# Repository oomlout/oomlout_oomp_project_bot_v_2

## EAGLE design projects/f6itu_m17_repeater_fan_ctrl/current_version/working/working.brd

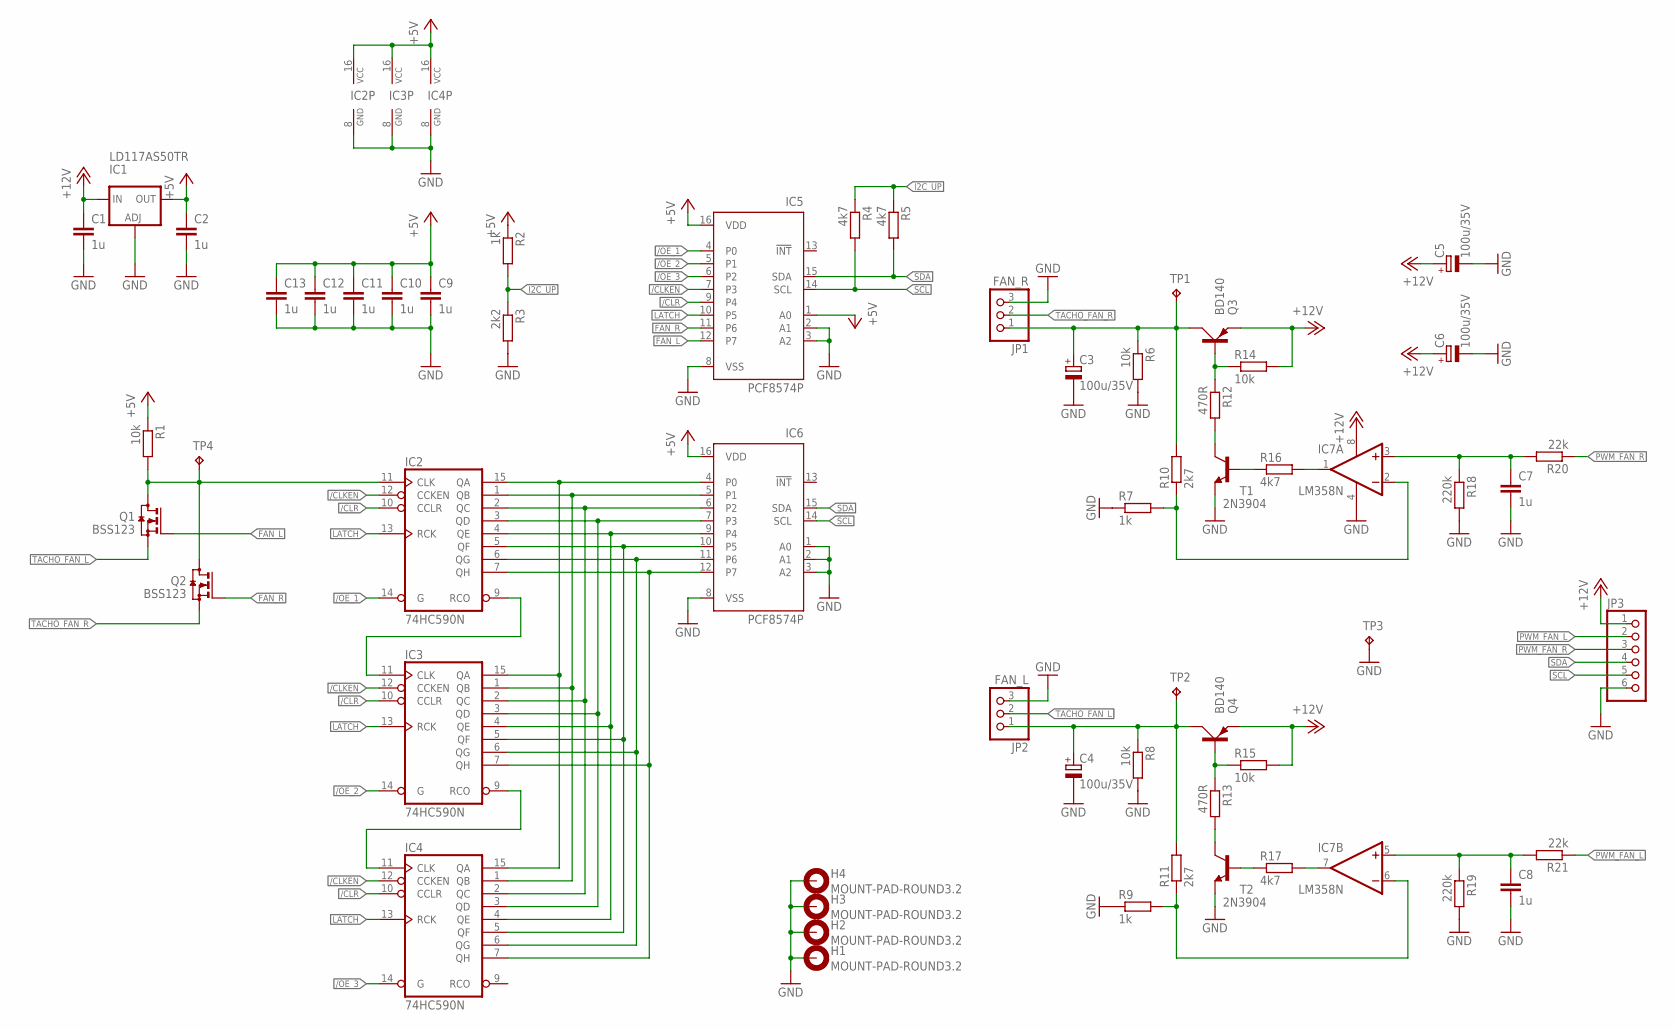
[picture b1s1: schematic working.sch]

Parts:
C1, C2, C7, C8, C9, C10, C11, C12, C13: 1u; C0805
C3, C4, C5, C6: 100u/35V; E3,5-8
H1, H2, H3, H4: MOUNT-PAD-ROUND3.2; 3,2-PAD
IC1: LD117AS50TR; SOT223
IC2, IC3, IC4: 74HC590N; DIL16
IC5, IC6: PCF8574P; DIL16
IC7: LM358N; DIL08
JP1: FAN_R; 1X03
JP2: FAN_L; 1X03
JP3: PINHD-1X6; 1X06
Q1, Q2: BSS123; SOT23
Q3, Q4: BD140; TO126AV
R1, R6, R8, R14, R15: 10k; R0805
R2, R7, R9: 1k; R0805
R3: 2k2; R0805
R4, R5, R16, R17: 4k7; R0805
R10, R11: 2k7; R0805
R12, R13: 470R; R0805
R18, R19: 220k; R0805
R20, R21: 22k; R0805
T1, T2: 2N3904; TO92-EBC
TP1, TP2, TP3, TP4: TPB2,54; B2,54

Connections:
+5V: C2.1, C9.1, C10.1, C11.1, C12.1, C13.1, IC1.4 (OUT), IC2.16 (VCC), IC3.16 (VCC), IC4.16 (VCC), IC5.1 (A0), IC5.16 (VDD), IC6.16 (VDD), R1.1, R2.1
+12V: C1.1, C5.+, C6.+, IC1.3 (IN), IC7.8 (V+), JP3.1, Q3.E, Q4.E, R14.2, R15.2
/CLKEN: IC2.12 (CCKEN), IC3.12 (CCKEN), IC4.12 (CCKEN), IC5.7 (P3)
/CLR: IC2.10 (CCLR), IC3.10 (CCLR), IC4.10 (CCLR), IC5.9 (P4)
/OE_1: IC2.14 (G), IC5.4 (P0)
/OE_2: IC3.14 (G), IC5.5 (P1)
/OE_3: IC4.14 (G), IC5.6 (P2)
FAN_L: IC5.12 (P7), Q1.1 (G)
FAN_R: IC5.11 (P6), Q2.1 (G)
GND: C1.2, C2.2, C3.-, C4.-, C5.-, C6.-, C7.2, C8.2, C9.2, C10.2, C11.2, C12.2, C13.2, H1.B3,2, H2.B3,2, H3.B3,2, H4.B3,2, IC1.1 (ADJ), IC2.8 (GND), IC3.8 (GND), IC4.8 (GND), IC5.2 (A1), IC5.3 (A2), IC5.8 (VSS), IC6.1 (A0), IC6.2 (A1), IC6.3 (A2), IC6.8 (VSS), IC7.4 (V-), JP1.3, JP2.3, JP3.6, R3.2, R6.2, R7.1, R8.2, R9.1, R18.2, R19.2, T1.E, T2.E, TP3.TP
I2C_UP: R2.2, R3.1, R4.1, R5.1
LATCH: IC2.13 (RCK), IC3.13 (RCK), IC4.13 (RCK), IC5.10 (P5)
unnamed: IC2.15 (QA), IC3.15 (QA), IC4.15 (QA), IC6.4 (P0)
unnamed: IC2.1 (QB), IC3.1 (QB), IC4.1 (QB), IC6.5 (P1)
unnamed: IC2.2 (QC), IC3.2 (QC), IC4.2 (QC), IC6.6 (P2)
unnamed: IC2.3 (QD), IC3.3 (QD), IC4.3 (QD), IC6.7 (P3)
unnamed: IC2.4 (QE), IC3.4 (QE), IC4.4 (QE), IC6.9 (P4)
unnamed: IC2.11 (CLK), Q1.3 (D), Q2.3 (D), R1.2, TP4.TP
unnamed: IC2.6 (QG), IC3.6 (QG), IC4.6 (QG), IC6.11 (P6)
unnamed: C7.1, IC7.3 (+IN), R18.1, R20.2
unnamed: R12.2, T1.C
unnamed: C8.1, IC7.5 (+IN), R19.1, R21.2
unnamed: Q3.B, R12.1, R14.1
unnamed: IC3.9 (RCO), IC4.11 (CLK)
unnamed: R13.2, T2.C
unnamed: C3.+, JP1.1, Q3.C, R6.1, R10.2, TP1.TP
unnamed: IC7.6 (-IN), R9.2, R11.1
unnamed: Q4.B, R13.1, R15.1
unnamed: R16.1, T1.B
unnamed: C4.+, JP2.1, Q4.C, R8.1, R11.2, TP2.TP
unnamed: IC7.2 (-IN), R7.2, R10.1
unnamed: IC7.1 (OUT), R16.2
unnamed: R17.1, T2.B
unnamed: IC7.7 (OUT), R17.2
unnamed: IC2.9 (RCO), IC3.11 (CLK)
unnamed: IC2.5 (QF), IC3.5 (QF), IC4.5 (QF), IC6.10 (P5)
unnamed: IC2.7 (QH), IC3.7 (QH), IC4.7 (QH), IC6.12 (P7)
PWM_FAN_L: JP3.2, R21.1
PWM_FAN_R: JP3.3, R20.1
SCL: IC5.14 (SCL), IC6.14 (SCL), JP3.5, R4.2
SDA: IC5.15 (SDA), IC6.15 (SDA), JP3.4, R5.2
TACHO_FAN_L: JP2.2, Q1.2 (S)
TACHO_FAN_R: JP1.2, Q2.2 (S)

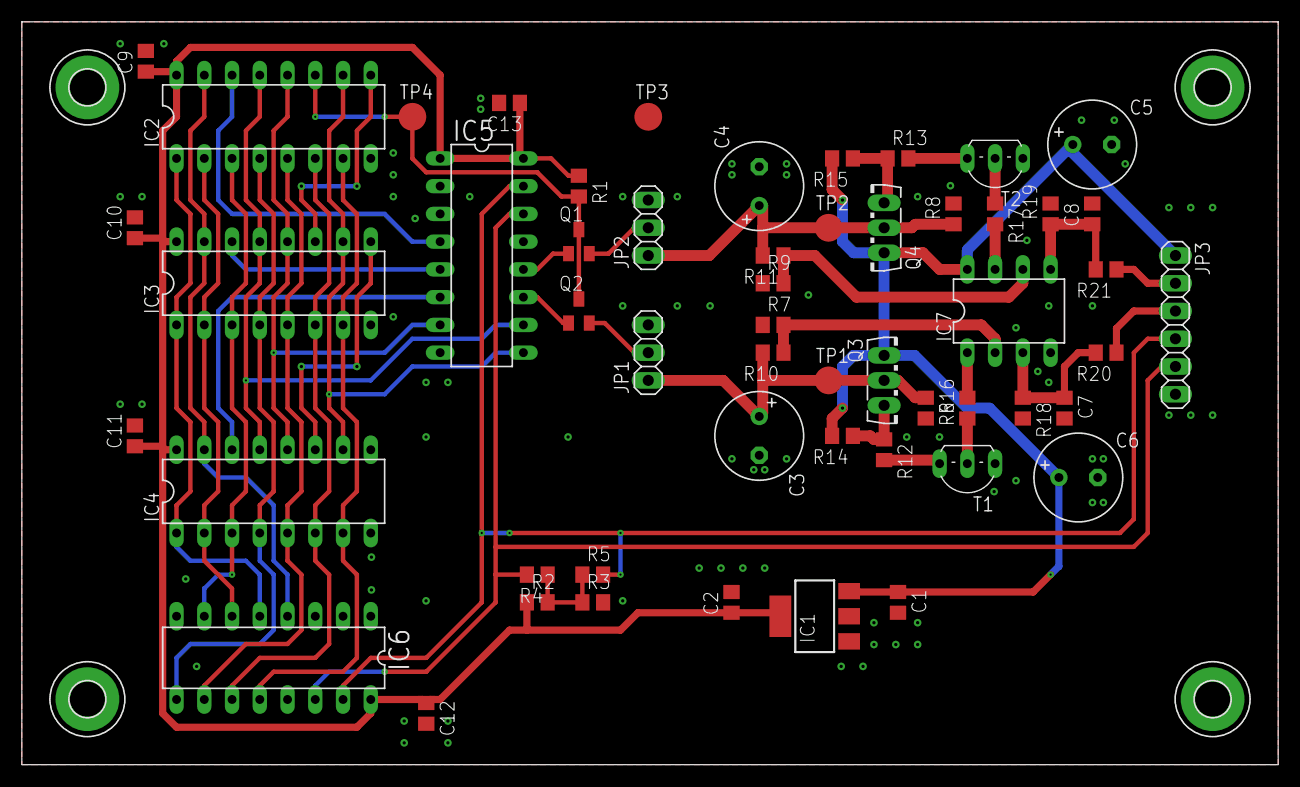
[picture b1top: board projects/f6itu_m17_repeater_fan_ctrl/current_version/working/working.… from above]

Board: 2 copper layers, 115.0 x 68.0 mm, 58 parts (0 on the bottom side), 43 nets.

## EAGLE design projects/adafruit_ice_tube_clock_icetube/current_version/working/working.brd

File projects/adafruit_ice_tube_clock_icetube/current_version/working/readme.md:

# ice_tube_clock
 
## summary 
* id: adafruit_ice_tube_clock_icetube
* user: adafruit
* name: ice_tube_clock
* board: icetube
* repo: https://github.com/adafruit/Ice-Tube-Clock

* src_file_repo_sch: 
* src_file_repo_sch_link: https://github.com/adafruit/Ice-Tube-Clock/tree/master/
* full details link: https://github.com/oomlout/oomlout_oomp_project_bot_v_2/tree/main/projects/adafruit_ice_tube_clock_icetube/current_version/working  

## pcb  

[board (pdf)](working.pdf)

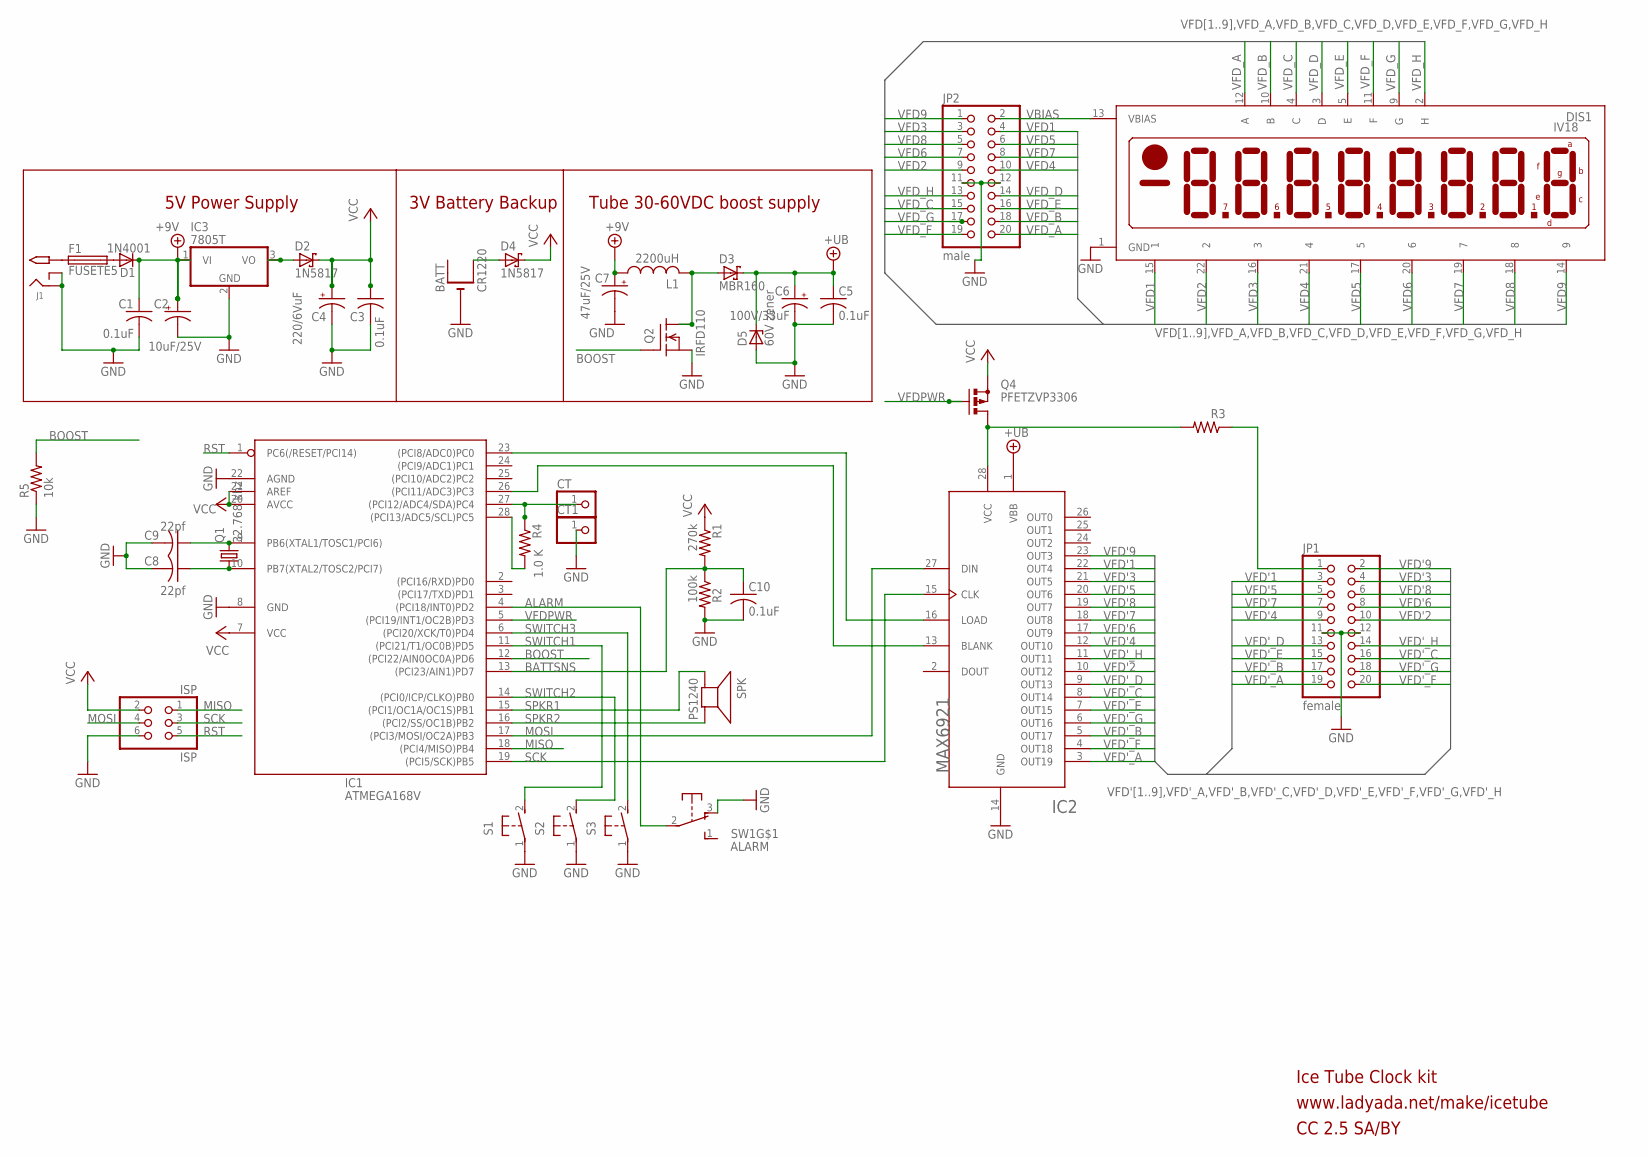
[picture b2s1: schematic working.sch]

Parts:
BATT: CR1220; CR1220-THM
C1, C3: 0.1uF; C025-025X050
C2: 10uF/25V; E2,5-6
C4: 220/6VuF; E2,5-6
C5, C10: 0.1uF; C025-024X044
C6: 100V/33uF; E3,5-8
C7: 47uF/25V; E2,5-6
C8, C9: 22pf; C025-025X050
CT, CT1: PINHD-1X1; 1X01
D1: 1N4001; DO41-10
D2, D4: 1N5817; DO41-10
D3: MBR160; DO41-10
D5: 60V zener; DO41Z10
DIS1: IV18
F1: FUSETE5; TE5
IC1: ATMEGA168V; DIL28/3
IC2: MAX6921; PLCC-S28
IC3: 7805T; TO220H
ISP: ISP; 2X03
J1: 2.1MMJACK; PJ-102A
JP1: female; 2X10
JP2: male; 2X10
L1: 2200uH; 6000
Q1: 32.768 khz; TC26V
Q2: IRFD110; DIL04
Q4: PFETZVP3306; TO92-OVAL
R1: 270k; 0207/10
R2: 100k; 0207/10
R3: 22; 0207/10
R4: 1.0 K; 0207/5V
R5: 10k; 0207/5V
S1, S2, S3: 31-XX; B3F-31XX
SPK: PS1240; PS12
SW1: ALARM; OS102011MA1Q

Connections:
+9V: C1.1, C2.+, C7.+, D1.C, IC3.1 (VI), L1.1
+UB: C5.1, C6.+, D3.C, D5.C, IC2.1 (VBB)
ALARM: IC1.4 ((PCI18/INT0)PD2), SW1.2
BATTSNS: C10.1, IC1.13 ((PCI23/AIN1)PD7), R1.2, R2.1
BLANK: IC1.26 ((PCI11/ADC3)PC3), IC2.13 (BLANK)
BOOST: IC1.12 ((PCI22/AIN0OC0A)PD6), Q2.3 (G), R5.2
GND: BATT.-, C1.2, C2.-, C3.2, C4.-, C5.2, C6.-, C7.-, C8.2, C9.2, C10.2, CT1.1, D5.A, DIS1.1 (GND), IC1.8 (GND), IC1.22 (AGND), IC2.14 (GND), IC3.2 (GND), ISP.6, J1.RING, J1.RING_SW, JP1.11, JP1.12, JP2.11, JP2.12, Q2.4 (S), R2.2, R5.1, S1.1, S2.1, S3.1, SW1.3 (O)
LOAD: IC1.23 ((PCI8/ADC0)PC0), IC2.16 (LOAD)
MISO: IC1.18 ((PCI4/MISO)PB4), ISP.1
MOSI: IC1.17 ((PCI3/MOSI/OC2A)PB3), IC2.27 (DIN), ISP.4
unnamed: C9.1, IC1.9 (PB6(XTAL1/TOSC1/PCI6)), Q1.2
unnamed: D3.A, L1.2, Q2.1 (D), Q2.2 (D1)
unnamed: C8.1, IC1.10 (PB7(XTAL2/TOSC2/PCI7)), Q1.1
unnamed: F1.1, J1.TIP
unnamed: D1.A, F1.2
unnamed: BATT.+2 (+1), D4.A
unnamed: IC1.28 ((PCI13/ADC5/SCL)PC5), R4.2
unnamed: JP1.1, R3.1
unnamed: IC2.28 (VCC), Q4.3 (D), R3.2
unnamed: CT.1, IC1.27 ((PCI12/ADC4/SDA)PC4), R4.1
unnamed: D2.A, IC3.3 (VO)
RST: IC1.1 (PC6(/RESET/PCI14)), ISP.5
SCK: IC1.19 ((PCI5/SCK)PB5), IC2.15 (CLK), ISP.3
SPKR1: IC1.15 ((PCI1/OC1A/OC1S)PB1), SPK.P$1 (+)
SPKR2: IC1.16 ((PCI2/SS/OC1B)PB2), SPK.P$2 (-)
SWITCH1: IC1.11 ((PCI21/T1/OC0B)PD5), S1.2 (S)
SWITCH2: IC1.14 ((PCI0/ICP/CLKO)PB0), S2.2 (S)
SWITCH3: IC1.6 ((PCI20/XCK/T0)PD4), S3.2 (S)
VBIAS: DIS1.13 (VBIAS), JP2.2
VCC: C3.1, C4.+, D2.C, D4.C, IC1.7 (VCC), IC1.20 (AVCC), IC1.21 (AREF), ISP.2, Q4.1 (S), R1.1
VFD1: DIS1.15 (1), JP2.4
VFD2: DIS1.22 (2), JP2.9
VFD3: DIS1.16 (3), JP2.3
VFD4: DIS1.21 (4), JP2.10
VFD5: DIS1.17 (5), JP2.6
VFD6: DIS1.20 (6), JP2.7
VFD7: DIS1.19 (7), JP2.8
VFD8: DIS1.18 (8), JP2.5
VFD9: DIS1.14 (9), JP2.1
VFD'1: IC2.22 (OUT4), JP1.3
VFD'2: IC2.10 (OUT12), JP1.10
VFD'3: IC2.21 (OUT5), JP1.4
VFD'4: IC2.12 (OUT10), JP1.9
VFD'5: IC2.20 (OUT6), JP1.5
VFD'6: IC2.17 (OUT9), JP1.8
VFD'7: IC2.18 (OUT8), JP1.7
VFD'8: IC2.19 (OUT7), JP1.6
VFD'9: IC2.23 (OUT3), JP1.2
VFD'_A: IC2.3 (OUT19), JP1.19
VFD'_B: IC2.5 (OUT17), JP1.17
VFD'_C: IC2.8 (OUT14), JP1.16
VFD'_D: IC2.9 (OUT13), JP1.13
VFD'_E: IC2.7 (OUT15), JP1.15
VFD'_F: IC2.4 (OUT18), JP1.20
VFD'_G: IC2.6 (OUT16), JP1.18
VFD'_H: IC2.11 (OUT11), JP1.14
VFDPWR: IC1.5 ((PCI19/INT1/OC2B)PD3), Q4.2 (G)
VFD_A: DIS1.12 (A), JP2.20
VFD_B: DIS1.10 (B), JP2.18
VFD_C: DIS1.4 (C), JP2.15
VFD_D: DIS1.3 (D), JP2.14
VFD_E: DIS1.5 (E), JP2.16
VFD_F: DIS1.11 (F), JP2.19
VFD_G: DIS1.9 (G), JP2.17
VFD_H: DIS1.2 (H), JP2.13

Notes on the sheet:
5V Power Supply
3V Battery Backup
Tube 30-60VDC boost supply
Ice Tube Clock kit
www.ladyada.net/make/icetube
CC 2.5 SA/BY

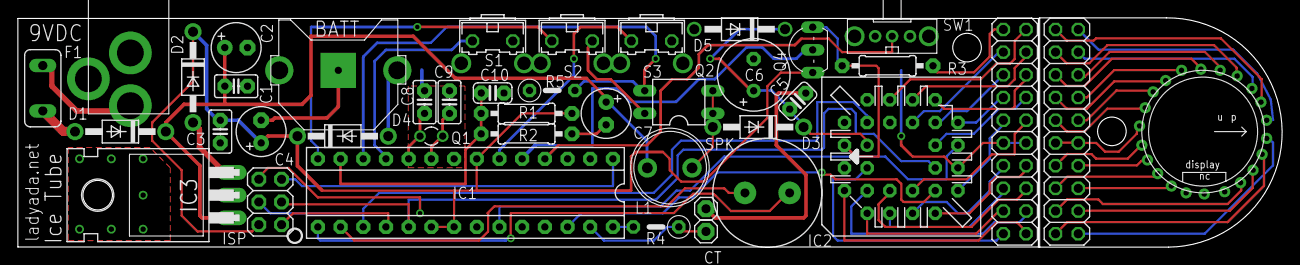
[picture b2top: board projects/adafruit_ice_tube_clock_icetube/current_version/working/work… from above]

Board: 2 copper layers, 141.5 x 25.7 mm, 41 parts (0 on the bottom side), 65 nets.

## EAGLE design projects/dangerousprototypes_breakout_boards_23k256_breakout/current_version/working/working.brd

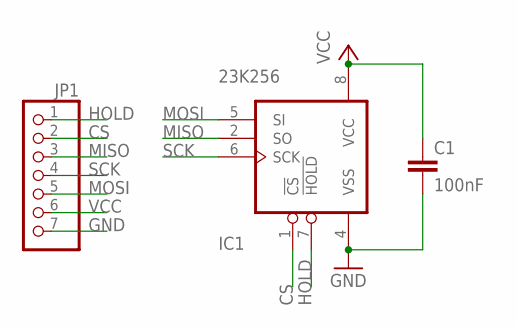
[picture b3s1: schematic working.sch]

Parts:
C1: 100nF; C805
IC1: 23K256; SOIC8
JP1: PINHD-1X7; 1X07

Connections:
CS: IC1.1 (!CS), JP1.2
GND: C1.2, IC1.4 (VSS), JP1.7
HOLD: IC1.7 (!HOLD), JP1.1
MISO: IC1.2 (SO), JP1.3
MOSI: IC1.5 (SI), JP1.5
SCK: IC1.6 (SCK), JP1.4
VCC: C1.1, IC1.8 (VCC), JP1.6

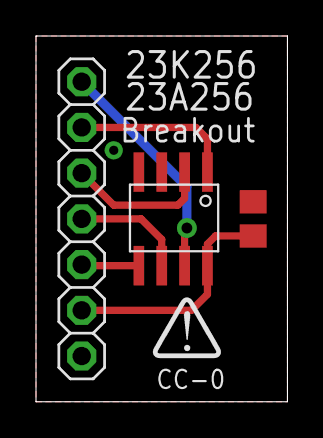
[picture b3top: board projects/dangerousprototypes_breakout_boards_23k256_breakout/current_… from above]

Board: 2 copper layers, 14.0 x 20.3 mm, 4 parts (0 on the bottom side), 7 nets.

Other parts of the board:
U$1: DP_LOGO

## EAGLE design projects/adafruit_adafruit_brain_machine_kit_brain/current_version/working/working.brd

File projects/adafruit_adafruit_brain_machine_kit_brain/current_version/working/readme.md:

# adafruit_brain_machine_kit
 
## summary 
* id: adafruit_adafruit_brain_machine_kit_brain
* user: adafruit
* name: adafruit_brain_machine_kit
* board: brain
* repo: https://github.com/adafruit/Adafruit_Brain-Machine-Kit

* src_file_repo_sch: 
* src_file_repo_sch_link: https://github.com/adafruit/Adafruit_Brain-Machine-Kit/tree/master/
* full details link: https://github.com/oomlout/oomlout_oomp_project_bot_v_2/tree/main/projects/adafruit_adafruit_brain_machine_kit_brain/current_version/working  

## pcb  

[board (pdf)](working.pdf)

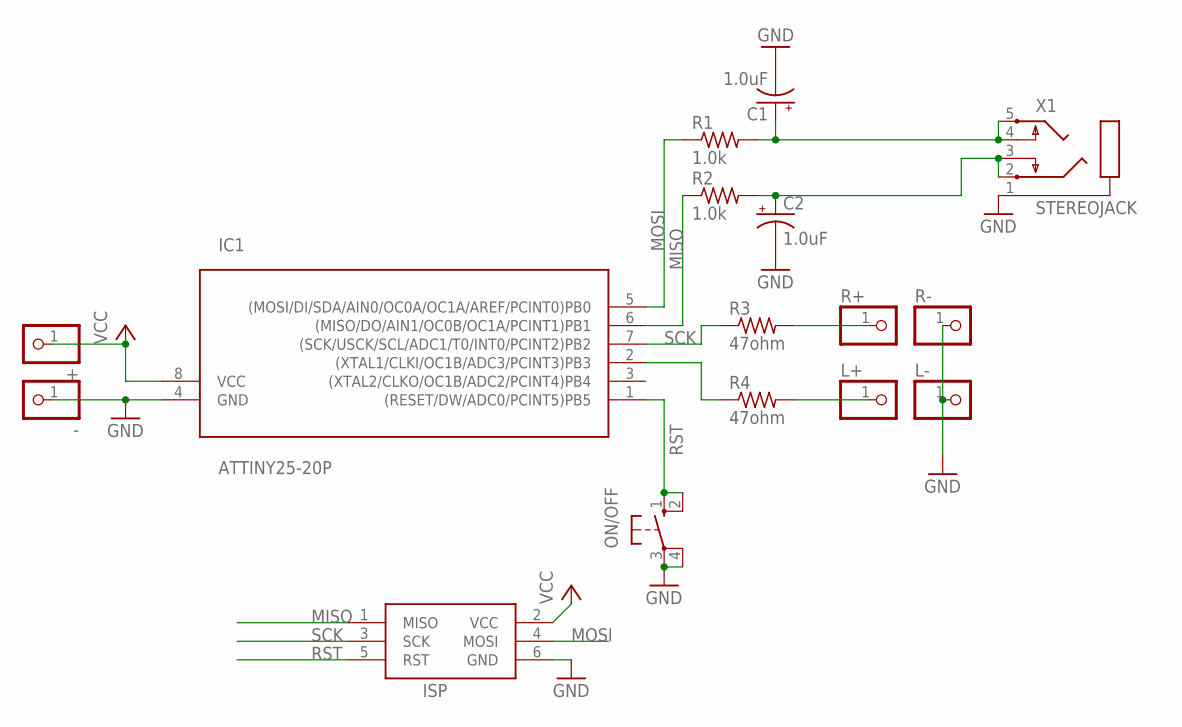
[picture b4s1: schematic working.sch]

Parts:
+: PINHD-1X1; 1X01
-: PINHD-1X1; 1X01
C1, C2: 1.0uF; E2,5-5
IC1: ATTINY25-20P; DIL08
ISP: AVRISP-6; AVRISP
L+: PINHD-1X1; 1X01
L-: PINHD-1X1; 1X01
ON/OFF: 10-XX; B3F-10XX
R1, R2: 1.0k; 0207/10
R3, R4: 47ohm; 0207/10
R+: PINHD-1X1; 1X01
R-: PINHD-1X1; 1X01
X1: STEREOJACK; STX3100

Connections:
GND: -.1, C1.-, C2.-, IC1.4 (GND), ISP.6 (GND), L-.1, ON/OFF.3, ON/OFF.4 (P1), R-.1, X1.1
LEYE+: L+.1, R4.2
MISO: IC1.6 ((MISO/DO/AIN1/OC0B/OC1A/PCINT1)PB1), ISP.1 (MISO), R2.1
MOSI: IC1.5 ((MOSI/DI/SDA/AIN0/OC0A/OC1A/AREF/PCINT0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), ISP.4 (MOSI), R1.1
unnamed: C1.+, R1.2, X1.4, X1.5
unnamed: C2.+, R2.2, X1.2, X1.3
unnamed: IC1.2 ((XTAL1/CLKI/OC1B/ADC3/PCINT3)PB3), R4.1
unnamed: R3.2, R+.1
RST: IC1.1 ((RESET/DW/ADC0/PCINT5)PB5), ISP.5 (RST), ON/OFF.1 (S), ON/OFF.2 (S1)
SCK: IC1.7 ((SCK/USCK/SCL/ADC1/T0/INT0/PCINT2)PB2), ISP.3 (SCK), R3.1
VCC: +.1, IC1.8 (VCC), ISP.2 (VCC)

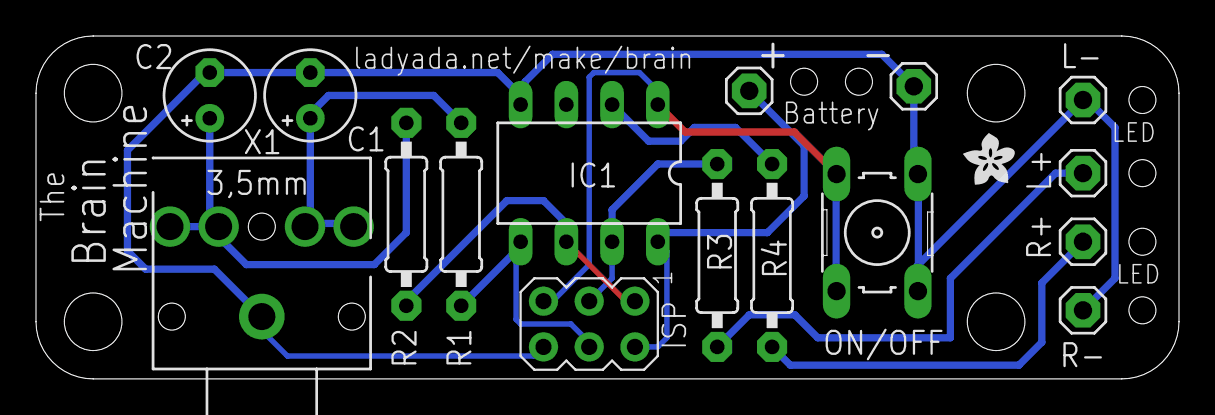
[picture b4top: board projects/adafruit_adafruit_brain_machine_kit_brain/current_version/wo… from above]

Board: 2 copper layers, 63.5 x 19.1 mm, 17 parts (0 on the bottom side), 11 nets.

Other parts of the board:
U$1: ADAFRUIT200MIL

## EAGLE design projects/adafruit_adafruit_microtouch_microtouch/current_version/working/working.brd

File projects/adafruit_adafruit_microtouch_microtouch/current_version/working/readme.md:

# adafruit_microtouch
 
## summary 
* id: adafruit_adafruit_microtouch_microtouch
* user: adafruit
* name: adafruit_microtouch
* board: microtouch
* repo: https://github.com/adafruit/Adafruit_Microtouch

* src_file_repo_sch: 
* src_file_repo_sch_link: https://github.com/adafruit/Adafruit_Microtouch/tree/master/
* full details link: https://github.com/oomlout/oomlout_oomp_project_bot_v_2/tree/main/projects/adafruit_adafruit_microtouch_microtouch/current_version/working  

## schematic  
  
[schematic (pdf)](working_schematic.pdf) 

## pcb  

[board (pdf)](working.pdf)  

## working_bom
| Id | Designator | Footprint | Quantity | Designation | Supplier and ref |  | None | 
| --- | --- | --- | --- | --- | --- | --- | --- | 
| 1 | U2 | KSSMINI | 1 | KSSMINISWITCH |  |  | [''] | 
| 2 | R5,R7 | R0805 | 2 | 1k |  |  | [''] | 
| 3 | LED1 | CHIPLED_0805 | 1 | RED |  |  | [''] | 
| 4 | LIPO0 | SOT23-5L | 1 | MCP73811/2 |  |  | [''] | 
| 5 | U1 | MICRO-SD-SOCKET-PP | 1 | MICROSD |  |  | [''] | 
| 6 | RESET/BOOT0 | EVQ-Q2 | 1 | EVQQ2 |  |  | [''] | 
| 7 | JP1 | JSTPH2 | 1 | BATT |  |  | [''] | 
| 8 | U$6,U$8,U$7 | FIDUCIAL_1MM | 3 | FIDUCIAL |  |  | [''] | 
| 9 | C2,C1 | C0805K | 2 | 18pf |  |  | [''] | 
| 10 | R1,R11,R2,R8,R9,R10 | R0805 | 6 | 22 |  |  | [''] | 
| 11 | X2 | NX5032 | 1 | 16Mhz |  |  | [''] | 
| 12 | C5,C8,C3,C6 | C0805K | 4 | 1uf |  |  | [''] | 
| 13 | R4,R14,R16 | R0805 | 3 | 10k |  |  | [''] | 
| 14 | ISP0 | MA03-2 | 1 | ISP |  |  | [''] | 
| 15 | U$1 | TQFP44 | 1 | ATMEGA32U4 |  |  | [''] | 
| 16 | U$9 | ADAFRUIT200MIL | 1 |  |  |  | [''] | 
| 17 | X1 | USB-MINIB | 1 | USBSMD |  |  | [''] | 
| 18 | R13,R12 | M0805 | 2 | 100K |  |  | [''] | 
| 19 | ACCELEROMERTER0 | LGA | 1 | MMA7455 |  |  | [''] | 
| 20 | R17 | M0805 | 1 | 4.7K |  |  | [''] | 
| 21 | R6 | R0805 | 1 | 100k |  |  | [''] | 
| 22 | C4 | A_3216-18R | 1 | 10uF |  |  | [''] | 
| 23 | LDO0 | SOT23-5L | 1 | LP298XS |  |  | [''] | 
| 24 | R3,R15 | M0805 | 2 | 10k |  |  | [''] | 
| 25 | Q1 | SOT23-BEC | 1 | PN2222 |  |  | [''] | 
| 26 | U$2 | LCD371MM | 1 | LCD37 |  |  | [''] | 

## bom_schematic
| Ref | Qnty | Value | Cmp name | Footprint | Description | Vendor | DNP | 
| --- | --- | --- | --- | --- | --- | --- | --- | 
| ACCELEROMERTER0 | 1 | MMA7455 | MMA7455 | working:LGA |  |  |  | 
| C1, C2 | 2 | 18pf | C-USC0805K | working:C0805K |  |  |  | 
| C3, C5, C6, C8 | 4 | 1uf | C-USC0805K | working:C0805K |  |  |  | 
| C4 | 1 | 10uF | CPOL-USA/3216-18R | working:A_3216-18R |  |  |  | 
| ISP0 | 1 | ISP | MA03-2 | working:MA03-2 |  |  |  | 
| JP1 | 1 | BATT | JST_2PIN | working:JSTPH2 |  |  |  | 
| LDO0 | 1 | LP298XS | LP298XS | working:SOT23-5L |  |  |  | 
| LED1 | 1 | RED | LED0805 | working:CHIPLED_0805 |  |  |  | 
| LIPO0 | 1 | MCP73811/2 | MCP73811/2 | working:SOT23-5L |  |  |  | 
| Q1 | 1 | PN2222 | -NPN-SOT23-BEC | working:SOT23-BEC |  |  |  | 
| R1, R2, R8, R9, R10, R11 | 6 | 22 | R-US_R0805 | working:R0805 |  |  |  | 
| R3, R15 | 2 | 10k | R-US_M0805 | working:M0805 |  |  |  | 
| R4, R14, R16 | 3 | 10k | R-US_R0805 | working:R0805 |  |  |  | 
| R5, R7 | 2 | 1k | R-US_R0805 | working:R0805 |  |  |  | 
| R6 | 1 | 100k | R-US_R0805 | working:R0805 |  |  |  | 
| R12, R13 | 2 | 100K | R-US_M0805 | working:M0805 |  |  |  | 
| R17 | 1 | 4.7K | R-US_M0805 | working:M0805 |  |  |  | 
| RESET/BOOT0 | 1 | EVQQ2 | EVQQ2 | working:EVQ-Q2 |  |  |  | 
| U1 | 1 | USD-SOCKETNEW | USD-SOCKETNEW | working:MICRO-SD-SOCKET-PP |  |  |  | 
| U2 | 1 | KSSMINISWITCH | KSSMINISWITCH | working:KSSMINI |  |  |  | 
| U$1 | 1 | ATMEGA32U4TQFP | ATMEGA32U4TQFP | working:TQFP44 |  |  |  | 
| U$2 | 1 | LCD37 | LCD37 | working:LCD371MM |  |  |  | 
| U$6, U$7, U$8 | 3 | FIDUCIAL | FIDUCIAL | working:FIDUCIAL_1MM |  |  |  | 
| X1 | 1 | USBSMD | USBMINIB | working:USB-MINIB |  |  |  | 
| X2 | 1 | 16Mhz | XTALNX5032 | working:NX5032 |  |  |  |

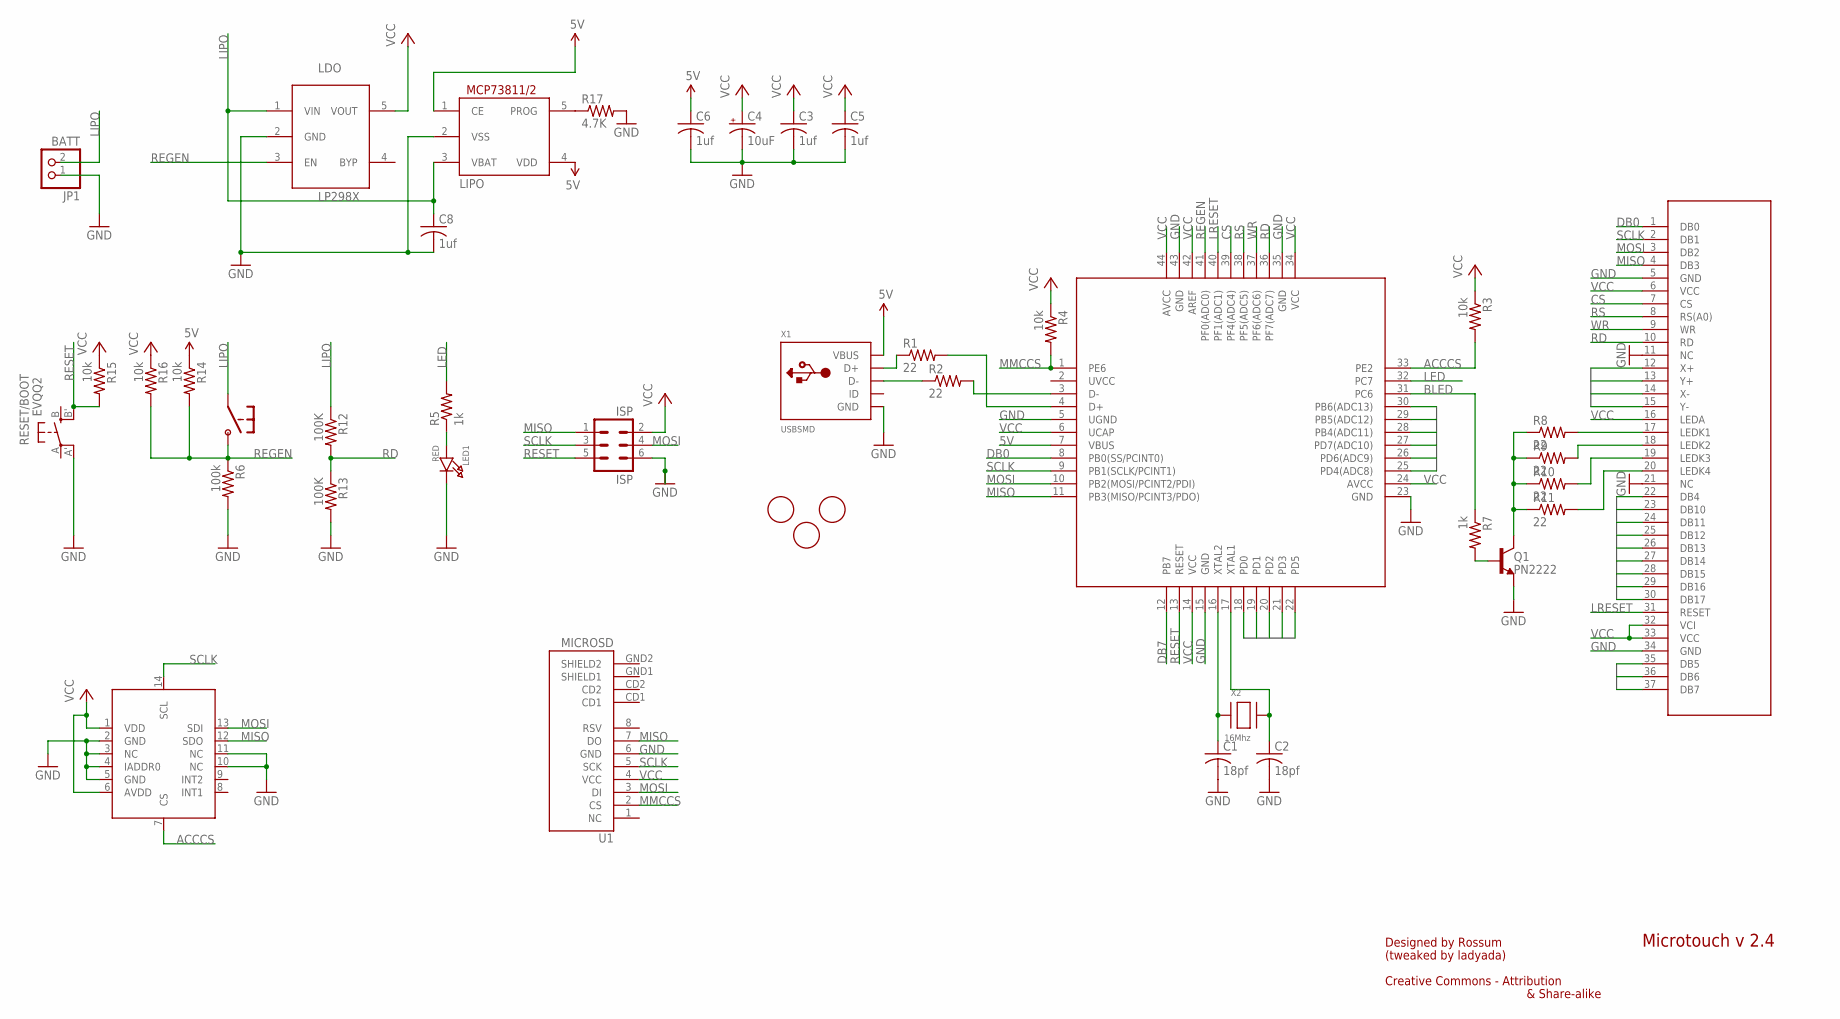
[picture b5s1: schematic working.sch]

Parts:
ACCELEROMERTER: MMA7455; LGA
C1, C2: 18pf; C0805K
C3, C5, C6, C8: 1uf; C0805K
C4: 10uF; A/3216-18R
ISP: ISP; MA03-2
JP1: BATT; JSTPH2
LDO: LP298XS; SOT23-5L
LED1: RED; CHIPLED_0805
LIPO: MCP73811/2; SOT23-5L
Q1: PN2222; SOT23-BEC
R1, R2, R8, R9, R10, R11: 22; R0805
R3, R15: 10k; M0805
R4, R14, R16: 10k; R0805
R5, R7: 1k; R0805
R6: 100k; R0805
R12, R13: 100K; M0805
R17: 4.7K; M0805
RESET/BOOT: EVQQ2; EVQ-Q2
U1: MICROSD; MICRO-SD-SOCKET-PP
U2: KSSMINISWITCH; KSSMINI
U$1: ATMEGA32U4; TQFP44
U$2: LCD37; LCD371MM
U$6, U$7, U$8: FIDUCIAL; FIDUCIAL_1MM
X1: USBSMD; USB-MINIB
X2: 16Mhz; NX5032

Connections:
5V: C6.1, LIPO.1 (CE), LIPO.4 (VDD), R14.1, U$1.7 (VBUS), X1.VBUS
ACCCS: ACCELEROMERTER.7 (CS), R3.2, U$1.33 (PE2)
BLED: R7.1, U$1.31 (PC6)
CS: U$1.39 (PF4(ADC4)), U$2.7 (CS)
DB0: U$1.8 (PB0(SS/PCINT0)), U$2.1 (DB0)
DB4: U$1.28 (PB4(ADC11)), U$2.12 (X+), U$2.22 (DB4)
DB5: U$1.29 (PB5(ADC12)), U$2.13 (Y+), U$2.35 (DB5)
DB6: U$1.30 (PB6(ADC13)), U$2.36 (DB6)
DB7: U$1.12 (PB7), U$2.37 (DB7)
DB8: U$1.18 (PD0), U$2.23 (DB10)
DB9: U$1.19 (PD1), U$2.24 (DB11)
DB10: U$1.20 (PD2), U$2.25 (DB12)
DB11: U$1.21 (PD3), U$2.26 (DB13)
DB12: U$1.25 (PD4(ADC8)), U$2.27 (DB14)
DB13: U$1.22 (PD5), U$2.28 (DB15)
DB14: U$1.26 (PD6(ADC9)), U$2.14 (X-), U$2.29 (DB16)
DB15: U$1.27 (PD7(ADC10)), U$2.15 (Y-), U$2.30 (DB17)
GND: ACCELEROMERTER.2 (GND), ACCELEROMERTER.3 (NC), ACCELEROMERTER.4 (IADDR0), ACCELEROMERTER.5 (GND), ACCELEROMERTER.10 (NC), ACCELEROMERTER.11 (NC), C1.2, C2.2, C3.2, C4.-, C5.2, C6.2, C8.2, ISP.6, JP1.1, LDO.2 (GND), LED1.C, LIPO.2 (VSS), Q1.E, R6.2, R13.2, R17.2, RESET/BOOT.A' (P1), U1.6 (GND), U$1.5 (UGND), U$1.15 (GND), U$1.23 (GND), U$1.35 (GND), U$1.43 (GND), U$2.5 (GND), U$2.11 (NC), U$2.21 (NC), U$2.34 (GND), X1.GND
LED: R5.2, U$1.32 (PC7)
LIPO: C8.1, JP1.2, LDO.1 (VIN), LIPO.3 (VBAT), R12.1, U2.P$1
LRESET: U$1.40 (PF1(ADC1)), U$2.31 (RESET)
MISO: ACCELEROMERTER.12 (SDO), ISP.1, U1.7 (DO), U$1.11 (PB3(MISO/PCINT3/PDO)), U$2.4 (DB3)
MMCCS: R4.2, U1.2 (CS), U$1.1 (PE6)
MOSI: ACCELEROMERTER.13 (SDI), ISP.4, U1.3 (DI), U$1.10 (PB2(MOSI/PCINT2/PDI)), U$2.3 (DB2)
unnamed: LIPO.5 (PROG), R17.1
unnamed: R1.1, X1.D+
unnamed: R2.1, X1.D-
unnamed: R10.2, U$2.19 (LEDK3)
unnamed: R8.2, U$2.17 (LEDK1)
unnamed: R9.2, U$2.18 (LEDK2)
unnamed: R11.2, U$2.20 (LEDK4)
unnamed: Q1.C, R8.1, R9.1, R10.1, R11.1
unnamed: Q1.B, R7.2
unnamed: LED1.A, R5.1
unnamed: R1.2, U$1.4 (D+)
unnamed: R2.2, U$1.3 (D-)
RD: R12.2, R13.1, U$1.36 (PF7(ADC7)), U$2.10 (RD)
REGEN: LDO.3 (EN), R6.1, R14.2, R16.2, U2.P$2, U$1.41 (PF0(ADC0))
RESET: ISP.5, R15.2, RESET/BOOT.B' (S1), U$1.13 (RESET)
RS: U$1.38 (PF5(ADC5)), U$2.8 (RS(A0))
SCLK: ACCELEROMERTER.14 (SCL), ISP.3, U1.5 (SCK), U$1.9 (PB1(SCLK/PCINT1)), U$2.2 (DB1)
VCC: ACCELEROMERTER.1 (VDD), ACCELEROMERTER.6 (AVDD), C3.1, C4.+, C5.1, ISP.2, LDO.5 (VOUT), R3.1, R4.1, R15.1, R16.1, U1.4 (VCC), U$1.6 (UCAP), U$1.14 (VCC), U$1.24 (AVCC), U$1.34 (VCC), U$1.42 (AREF), U$1.44 (AVCC), U$2.6 (VCC), U$2.16 (LEDA), U$2.32 (VCI), U$2.33 (VCC)
WR: U$1.37 (PF6(ADC6)), U$2.9 (WR)
XTAL1: C1.1, U$1.16 (XTAL2), X2.P$1
XTAL2: C2.1, U$1.17 (XTAL1), X2.P$2

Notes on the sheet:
Designed by Rossum
(tweaked by ladyada)
Microtouch v 2.4
Creative Commons - Attribution
& Share-alike

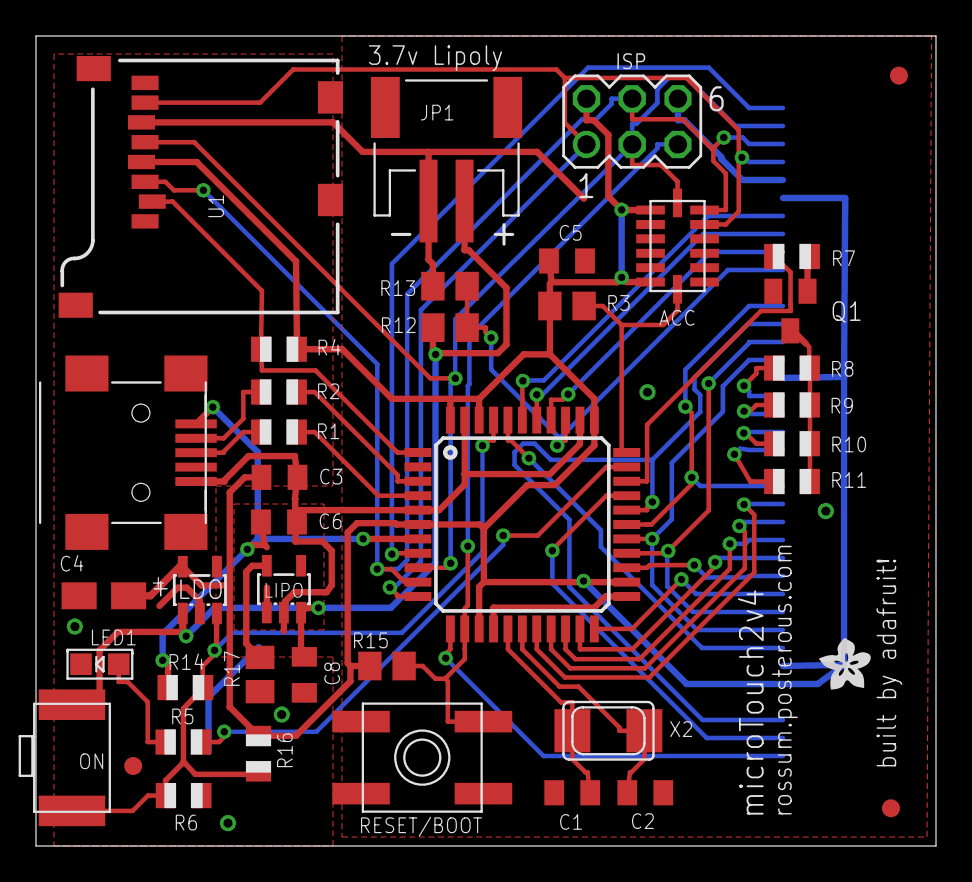
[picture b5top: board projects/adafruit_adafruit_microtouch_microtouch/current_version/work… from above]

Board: 2 copper layers, 50.0 x 45.0 mm, 42 parts (1 on the bottom side), 45 nets.

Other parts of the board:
U$9: ADAFRUIT200MIL

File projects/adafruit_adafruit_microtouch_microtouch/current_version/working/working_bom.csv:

"Id";"Designator";"Footprint";"Quantity";"Designation";"Supplier and ref";
1;"U2";"KSSMINI";1;"KSSMINISWITCH";;;
2;"R5,R7";"R0805";2;"1k";;;
3;"LED1";"CHIPLED_0805";1;"RED";;;
4;"LIPO0";"SOT23-5L";1;"MCP73811/2";;;
5;"U1";"MICRO-SD-SOCKET-PP";1;"MICROSD";;;
6;"RESET/BOOT0";"EVQ-Q2";1;"EVQQ2";;;
7;"JP1";"JSTPH2";1;"BATT";;;
8;"U$6,U$8,U$7";"FIDUCIAL_1MM";3;"FIDUCIAL";;;
9;"C2,C1";"C0805K";2;"18pf";;;
10;"R1,R11,R2,R8,R9,R10";"R0805";6;"22";;;
11;"X2";"NX5032";1;"16Mhz";;;
12;"C5,C8,C3,C6";"C0805K";4;"1uf";;;
13;"R4,R14,R16";"R0805";3;"10k";;;
14;"ISP0";"MA03-2";1;"ISP";;;
15;"U$1";"TQFP44";1;"ATMEGA32U4";;;
16;"U$9";"ADAFRUIT200MIL";1;"";;;
17;"X1";"USB-MINIB";1;"USBSMD";;;
18;"R13,R12";"M0805";2;"100K";;;
19;"ACCELEROMERTER0";"LGA";1;"MMA7455";;;
20;"R17";"M0805";1;"4.7K";;;
21;"R6";"R0805";1;"100k";;;
22;"C4";"A_3216-18R";1;"10uF";;;
23;"LDO0";"SOT23-5L";1;"LP298XS";;;
24;"R3,R15";"M0805";2;"10k";;;
25;"Q1";"SOT23-BEC";1;"PN2222";;;
26;"U$2";"LCD371MM";1;"LCD37";;;

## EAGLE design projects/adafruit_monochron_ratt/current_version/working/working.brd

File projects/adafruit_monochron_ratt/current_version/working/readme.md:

# monochron
 
## summary 
* id: adafruit_monochron_ratt
* user: adafruit
* name: monochron
* board: ratt
* repo: https://github.com/adafruit/monochron

* src_file_repo_sch: 
* src_file_repo_sch_link: https://github.com/adafruit/monochron/tree/master/
* full details link: https://github.com/oomlout/oomlout_oomp_project_bot_v_2/tree/main/projects/adafruit_monochron_ratt/current_version/working  

## pcb  

[board (pdf)](working.pdf)

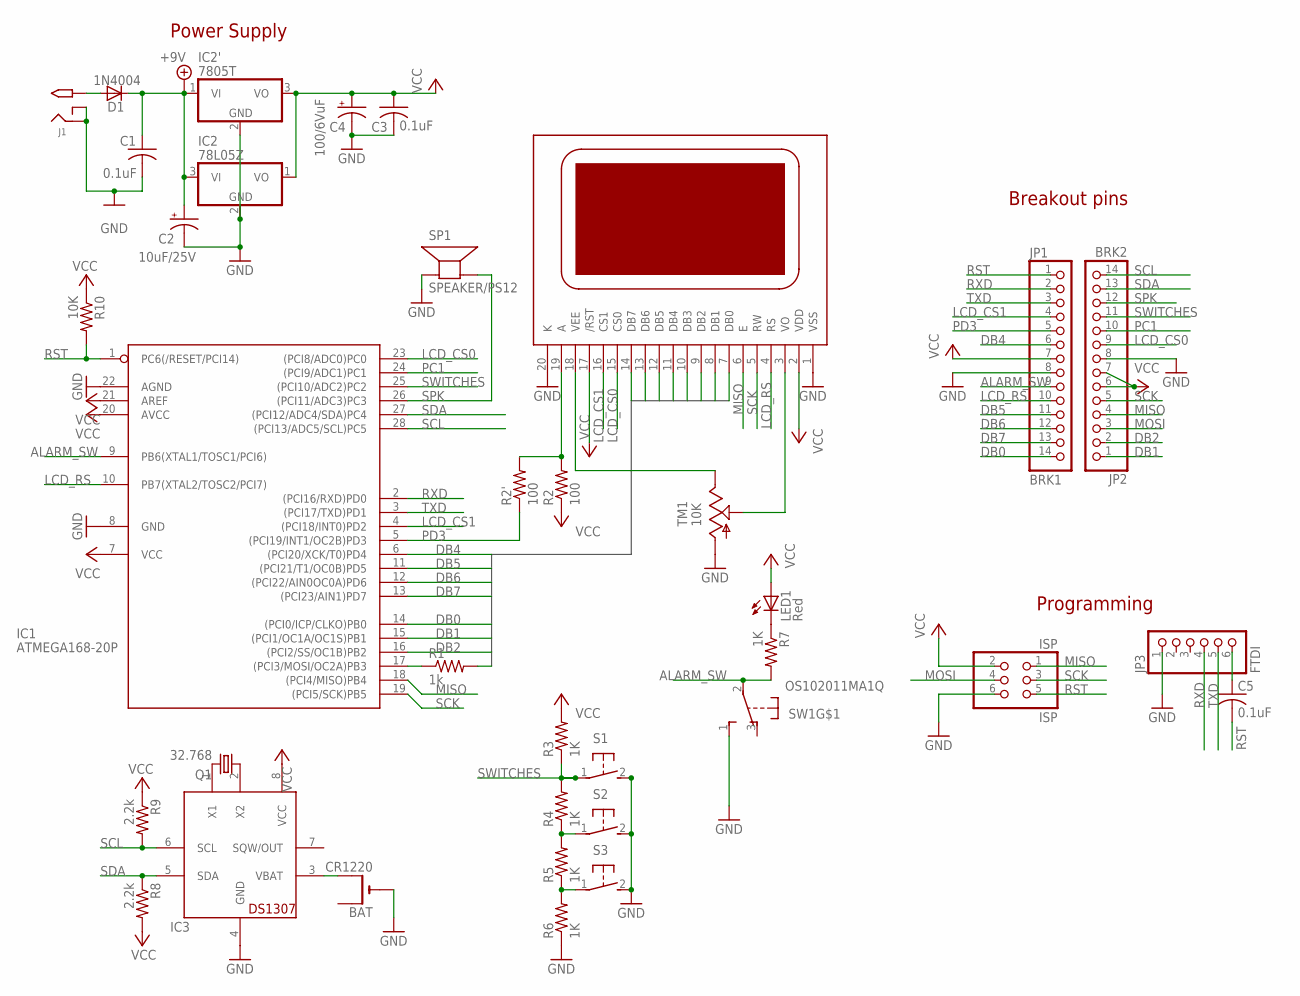
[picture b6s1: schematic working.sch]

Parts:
BAT: CR1220; CR1220-THM
C1, C3, C5: 0.1uF; C025-025X050
C2: 10uF/25V; E2,5-6E
C4: 100/6VuF; E2,5-6E
D1: 1N4004; DO41-10
IC1: ATMEGA168-20P; DIL28-3
IC2: 78L05Z; TO92
IC2': 7805T; TO220H
IC3: DS1307; DIL08
ISP: ISP; 2X03
J1: 2.1MMJACK; PJ-102A
JP1: BRK1; 1X14
JP2: BRK2; 1X14
JP3: FTDI; 1X06
LED1: Red; LED3MM
Q1: 32.768; TC38H
R1: 1k; 0207/10
R2, R2': 100; 0207/10
R3, R4, R5, R6, R7: 1K; 0207/10
R8, R9: 2.2k; 0207/10
R10: 10K; 0207/10
S1, S2, S3: 31-XX; B3F-31XX
SP1: SPEAKER/PS12; PS12
SW1: OS102011MA1Q
TM1: 10K; CA6H
U$1: TS12864A; TS12864

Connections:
+9V: C1.1, C2.+, D1.C, IC2.3 (VI), IC2'.1 (VI)
A: R2.2, R2'.2, U$1.19 (A)
ALARM_SW: IC1.9 (PB6(XTAL1/TOSC1/PCI6)), JP1.9, R7.2, SW1.2
DB0: IC1.14 ((PCI0/ICP/CLKO)PB0), JP1.14, U$1.7 (DB0)
DB1: IC1.15 ((PCI1/OC1A/OC1S)PB1), JP2.1, U$1.8 (DB1)
DB2: IC1.16 ((PCI2/SS/OC1B)PB2), JP2.2, U$1.9 (DB2)
DB3: R1.2, U$1.10 (DB3)
DB4: IC1.6 ((PCI20/XCK/T0)PD4), JP1.6, U$1.11 (DB4)
DB5: IC1.11 ((PCI21/T1/OC0B)PD5), JP1.11, U$1.12 (DB5)
DB6: IC1.12 ((PCI22/AIN0OC0A)PD6), JP1.12, U$1.13 (DB6)
DB7: IC1.13 ((PCI23/AIN1)PD7), JP1.13, U$1.14 (DB7)
GND: BAT.-, C1.2, C2.-, C3.2, C4.-, IC1.8 (GND), IC1.22 (AGND), IC2.2 (GND), IC2'.2 (GND), IC3.4 (GND), ISP.6, J1.RING, J1.RING_SW, JP1.8, JP2.8, JP3.1, R6.1, S1.2 (S), S2.2 (S), S3.2 (S), SP1.P$1 (+), SW1.1 (S), TM1.A, U$1.1 (VSS), U$1.20 (K)
LCD_CS0: IC1.23 ((PCI8/ADC0)PC0), JP2.9, U$1.15 (CS0)
LCD_CS1: IC1.4 ((PCI18/INT0)PD2), JP1.4, U$1.16 (CS1)
LCD_RS: IC1.10 (PB7(XTAL2/TOSC2/PCI7)), JP1.10, U$1.4 (RS)
MISO: IC1.18 ((PCI4/MISO)PB4), ISP.1, JP2.4, U$1.6 (E)
MOSI: IC1.17 ((PCI3/MOSI/OC2A)PB3), ISP.4, JP2.3, R1.1
unnamed: R4.1, R5.2, S2.1
unnamed: TM1.S, U$1.3 (VO)
unnamed: IC3.1 (X1), Q1.2
unnamed: IC3.2 (X2), Q1.1
unnamed: D1.A, J1.TIP
unnamed: BAT.+2 (+1), IC3.3 (VBAT)
unnamed: C5.1, JP3.6
unnamed: LED1.K (C), R7.1
unnamed: R5.1, R6.2, S3.1
PC1: IC1.24 ((PCI9/ADC1)PC1), JP2.10
PD3: IC1.5 ((PCI19/INT1/OC2B)PD3), JP1.5, R2'.1
RST: C5.2, IC1.1 (PC6(/RESET/PCI14)), ISP.5, JP1.1, R10.2
RXD: IC1.2 ((PCI16/RXD)PD0), JP1.2, JP3.4
SCK: IC1.19 ((PCI5/SCK)PB5), ISP.3, JP2.5, U$1.5 (RW)
SCL: IC1.28 ((PCI13/ADC5/SCL)PC5), IC3.6 (SCL), JP2.14, R9.2
SDA: IC1.27 ((PCI12/ADC4/SDA)PC4), IC3.5 (SDA), JP2.13, R8.1
SPK: IC1.26 ((PCI11/ADC3)PC3), JP2.12, SP1.P$2 (-)
SWITCHES: IC1.25 ((PCI10/ADC2)PC2), JP2.11, R3.1, R4.2, S1.1
TXD: IC1.3 ((PCI17/TXD)PD1), JP1.3, JP3.5
VCC: C3.1, C4.+, IC1.7 (VCC), IC1.20 (AVCC), IC1.21 (AREF), IC2.1 (VO), IC2'.3 (VO), IC3.8 (VCC), ISP.2, JP1.7, JP2.6, JP2.7, LED1.A, R2.1, R3.2, R8.2, R9.1, R10.1, U$1.2 (VDD), U$1.17 (/RST)
VEE: TM1.E, U$1.18 (VEE)

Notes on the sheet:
Power Supply
Programming
Breakout pins
